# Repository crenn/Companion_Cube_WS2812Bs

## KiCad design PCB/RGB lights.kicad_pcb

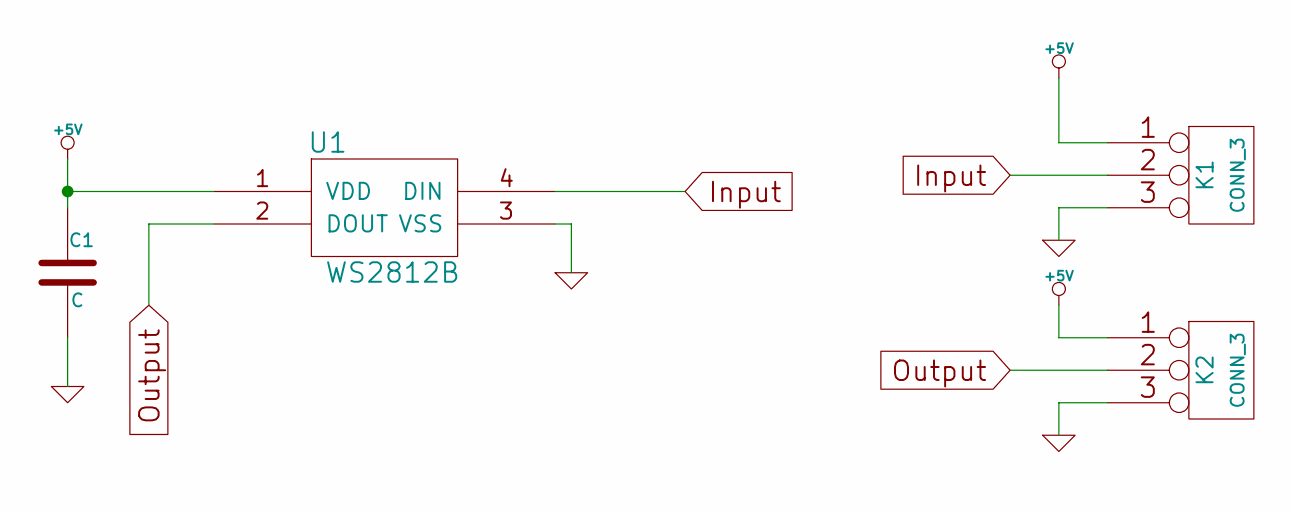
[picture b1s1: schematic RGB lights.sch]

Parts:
C1: C
K1, K2: CONN_3
U1: WS2812B

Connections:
+5V: C1.1, K1.1, K2.1, U1.1 (VDD)
GND: C1.2, K1.3, K2.3, U1.3 (VSS)
Input: K1.2 (PM), U1.4 (DIN)
Output: K2.2 (PM), U1.2 (DOUT)

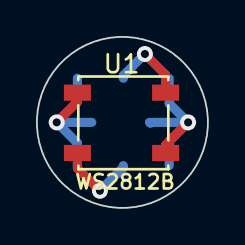
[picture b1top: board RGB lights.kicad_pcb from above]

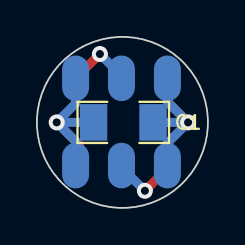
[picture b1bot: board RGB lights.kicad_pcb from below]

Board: 2 copper layers, 9.5 x 9.5 mm, 4 parts (3 on the bottom side), 4 nets.

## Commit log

2013-12-28 Initial Commit
    Add in PCB files
2013-12-28 Add current sketch that runs the lights
